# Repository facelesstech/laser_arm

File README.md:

# laser_arm
arduino controlled pan and tilt servo arm with a laser

Blog post - https://facelesstech.wordpress.com/2018/03/11/laser-arm/
Youtube - https://youtu.be/ycYnZCkt5O8

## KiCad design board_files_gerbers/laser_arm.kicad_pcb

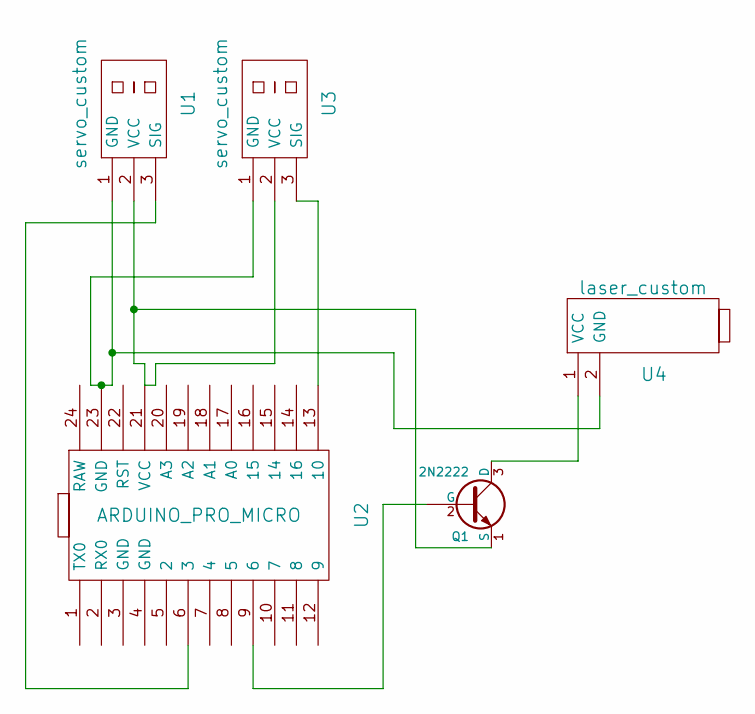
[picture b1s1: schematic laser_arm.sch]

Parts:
Q1: 2N2222
U1, U3: servo_custom
U2: ARDUINO_PRO_MICRO; arduino_leonardo
U4: laser_custom

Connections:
unnamed: Q1.1 (S), U1.2 (VCC), U2.21 (VCC), U3.2 (VCC)
unnamed: Q1.2 (G), U2.9 (6)
unnamed: Q1.3 (D), U4.1 (VCC)
unnamed: U1.1 (GND), U2.23 (GND), U3.1 (GND), U4.2 (GND)
unnamed: U1.3 (SIG), U2.6 (3)
unnamed: U2.13 (10), U3.3 (SIG)

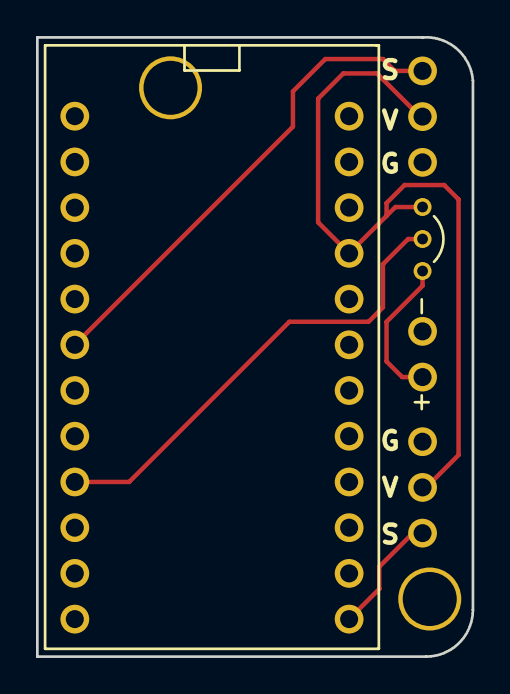
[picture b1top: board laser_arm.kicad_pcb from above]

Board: 2 copper layers, 24.2 x 34.4 mm, 5 parts (0 on the bottom side), 6 nets.

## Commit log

2018-03-11 arduino files
2018-03-11 Cleaned up the code
2018-03-11 board files and gerber
2018-03-17 added links
